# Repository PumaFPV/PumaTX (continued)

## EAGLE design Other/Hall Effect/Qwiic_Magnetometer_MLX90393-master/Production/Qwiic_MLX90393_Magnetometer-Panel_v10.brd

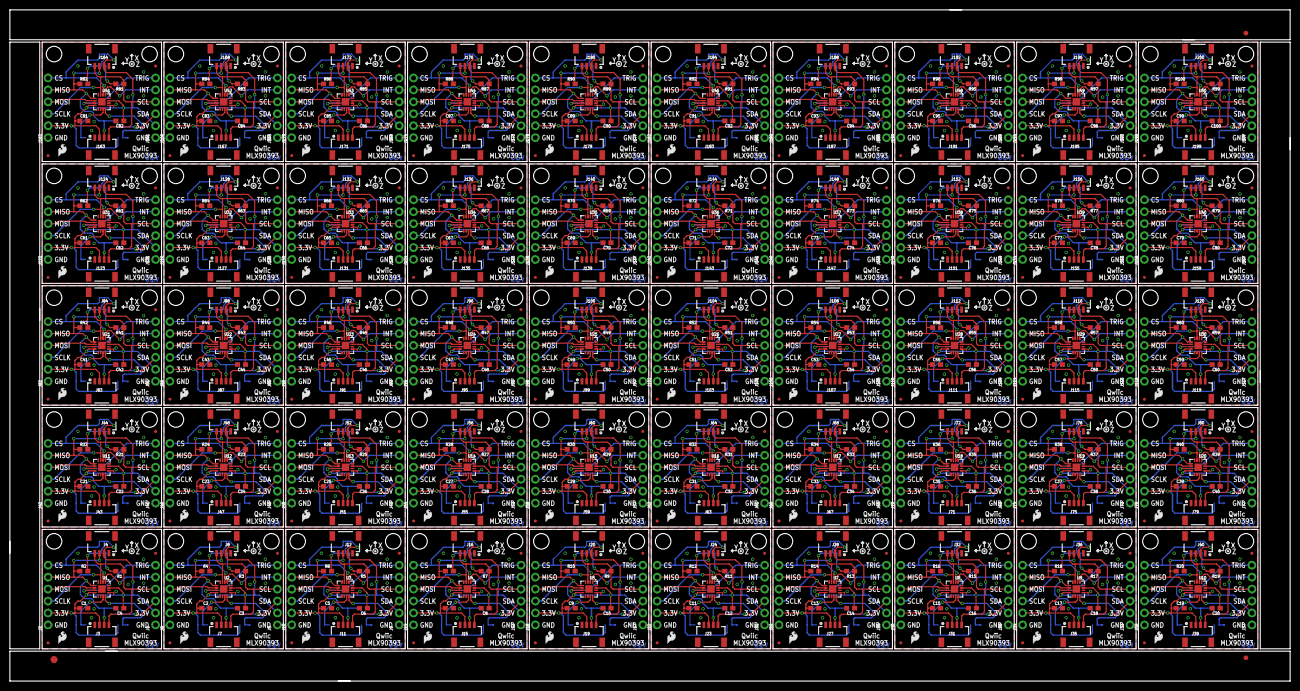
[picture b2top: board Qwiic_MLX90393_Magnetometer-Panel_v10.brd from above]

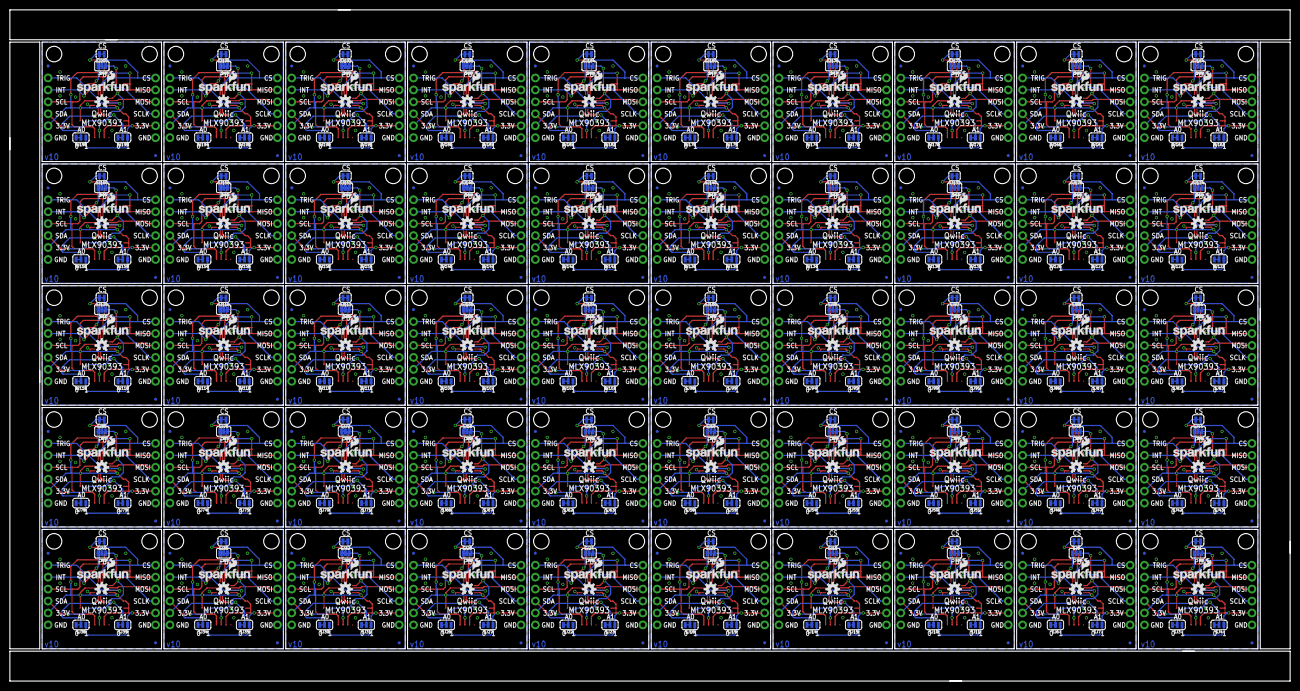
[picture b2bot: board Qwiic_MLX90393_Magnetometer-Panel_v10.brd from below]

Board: 2 copper layers, 272.3 x 142.7 mm, 1103 parts (400 on the bottom side), 600 nets.

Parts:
C1, C2, C3, C4, C5, C6, C7, C8, C9, C10, C11, C12, C13, C14, C15, C16, C17, C18, C19, C20, C21, C22, C23, C24, C25, C26, C27, C28, C29, C30, C31, C32, C33, C34, C35, C36, C37, C38, C39, C40, C41, C42, C43, C44, C45, C46, C47, C48, C49, C50, C51, C52, C53, C54, C55, C56, C57, C58, C59, C60, C61, C62, C63, C64, C65, C66, C67, C68, C69, C70, C71, C72, C73, C74, C75, C76, C77, C78, C79, C80, C81, C82, C83, C84, C85, C86, C87, C88, C89, C90, C91, C92, C93, C94, C95, C96, C97, C98, C99, C100: 0.1uF; 0603
E$1: FIDUCIAL-1.5X3
E$6, E$7: FIDUCIAL-1X2
FD1, FD2, FD3, FD4, FD5, FD6, FD7, FD8, FD9, FD10, FD11, FD12, FD13, FD14, FD15, FD16, FD17, FD18, FD19, FD20, FD21, FD22, FD23, FD24, FD25, FD26, FD27, FD28, FD29, FD30, FD31, FD32, FD33, FD34, FD35, FD36, FD37, FD38, FD39, FD40, FD41, FD42, FD43, FD44, FD45, FD46, FD47, FD48, FD49, FD50, FD51, FD52, FD53, FD54, FD55, FD56, FD57, FD58, FD59, FD60, FD61, FD62, FD63, FD64, FD65, FD66, FD67, FD68, FD69, FD70, FD71, FD72, FD73, FD74, FD75, FD76, FD77, FD78, FD79, FD80, FD81, FD82, FD83, FD84, FD85, FD86, FD87, FD88, FD89, FD90, FD91, FD92, FD93, FD94, FD95, FD96, FD97, FD98, FD99, FD100, FD101, FD102, FD103, FD104, FD105, FD106, FD107, FD108, FD109, FD110, FD111, FD112, FD113, FD114, FD115, FD116, FD117, FD118, FD119, FD120, FD121, FD122, FD123, FD124, FD125, FD126, FD127, FD128, FD129, FD130, FD131, FD132, FD133, FD134, FD135, FD136, FD137, FD138, FD139, FD140, FD141, FD142, FD143, FD144, FD145, FD146, FD147, FD148, FD149, FD150, FD151, FD152, FD153, FD154, FD155, FD156, FD157, FD158, FD159, FD160, FD161, FD162, FD163, FD164, FD165, FD166, FD167, FD168, FD169, FD170, FD171, FD172, FD173, FD174, FD175, FD176, FD177, FD178, FD179, FD180, FD181, FD182, FD183, FD184, FD185, FD186, FD187, FD188, FD189, FD190, FD191, FD192, FD193, FD194, FD195, FD196, FD197, FD198, FD199, FD200: FIDUCIALUFIDUCIAL; FIDUCIAL-MICRO
J1, J2, J5, J6, J9, J10, J13, J14, J17, J18, J21, J22, J25, J26, J29, J30, J33, J34, J37, J38, J41, J42, J45, J46, J49, J50, J53, J54, J57, J58, J61, J62, J65, J66, J69, J70, J73, J74, J77, J78, J81, J82, J85, J86, J89, J90, J93, J94, J97, J98, J101, J102, J105, J106, J109, J110, J113, J114, J117, J118, J121, J122, J125, J126, J129, J130, J133, J134, J137, J138, J141, J142, J145, J146, J149, J150, J153, J154, J157, J158, J161, J162, J165, J166, J169, J170, J173, J174, J177, J178, J181, J182, J185, J186, J189, J190, J193, J194, J197, J198: 1X06_NO_SILK
J3, J4, J7, J8, J11, J12, J15, J16, J19, J20, J23, J24, J27, J28, J31, J32, J35, J36, J39, J40, J43, J44, J47, J48, J51, J52, J55, J56, J59, J60, J63, J64, J67, J68, J71, J72, J75, J76, J79, J80, J83, J84, J87, J88, J91, J92, J95, J96, J99, J100, J103, J104, J107, J108, J111, J112, J115, J116, J119, J120, J123, J124, J127, J128, J131, J132, J135, J136, J139, J140, J143, J144, J147, J148, J151, J152, J155, J156, J159, J160, J163, J164, J167, J168, J171, J172, J175, J176, J179, J180, J183, J184, J187, J188, J191, J192, J195, J196, J199, J200: 1X04_1MM_RA
JP1, JP2, JP3, JP4, JP5, JP6, JP7, JP8, JP9, JP10, JP11, JP12, JP13, JP14, JP15, JP16, JP17, JP18, JP19, JP20, JP21, JP22, JP23, JP24, JP25, JP26, JP27, JP28, JP29, JP30, JP31, JP32, JP33, JP34, JP35, JP36, JP37, JP38, JP39, JP40, JP41, JP42, JP43, JP44, JP45, JP46, JP47, JP48, JP49, JP50, JP51, JP52, JP53, JP54, JP55, JP56, JP57, JP58, JP59, JP60, JP61, JP62, JP63, JP64, JP65, JP66, JP67, JP68, JP69, JP70, JP71, JP72, JP73, JP74, JP75, JP76, JP77, JP78, JP79, JP80, JP81, JP82, JP83, JP84, JP85, JP86, JP87, JP88, JP89, JP90, JP91, JP92, JP93, JP94, JP95, JP96, JP97, JP98, JP99, JP100: STAND-OFF
LOGO1, LOGO3, LOGO5, LOGO7, LOGO9, LOGO11, LOGO13, LOGO15, LOGO17, LOGO19, LOGO21, LOGO23, LOGO25, LOGO27, LOGO29, LOGO31, LOGO33, LOGO35, LOGO37, LOGO39, LOGO41, LOGO43, LOGO45, LOGO47, LOGO49, LOGO51, LOGO53, LOGO55, LOGO57, LOGO59, LOGO61, LOGO63, LOGO65, LOGO67, LOGO69, LOGO71, LOGO73, LOGO75, LOGO77, LOGO79, LOGO81, LOGO83, LOGO85, LOGO87, LOGO89, LOGO91, LOGO93, LOGO95, LOGO97, LOGO99: SFE_LOGO_NAME_FLAME.1_INCH; SFE_LOGO_NAME_FLAME_.1
LOGO2, LOGO4, LOGO6, LOGO8, LOGO10, LOGO12, LOGO14, LOGO16, LOGO18, LOGO20, LOGO22, LOGO24, LOGO26, LOGO28, LOGO30, LOGO32, LOGO34, LOGO36, LOGO38, LOGO40, LOGO42, LOGO44, LOGO46, LOGO48, LOGO50, LOGO52, LOGO54, LOGO56, LOGO58, LOGO60, LOGO62, LOGO64, LOGO66, LOGO68, LOGO70, LOGO72, LOGO74, LOGO76, LOGO78, LOGO80, LOGO82, LOGO84, LOGO86, LOGO88, LOGO90, LOGO92, LOGO94, LOGO96, LOGO98, LOGO100: SFE_LOGO_FLAME.1_INCH; SFE_LOGO_FLAME_.1
R1, R2, R3, R4, R5, R6, R7, R8, R9, R10, R11, R12, R13, R14, R15, R16, R17, R18, R19, R20, R21, R22, R23, R24, R25, R26, R27, R28, R29, R30, R31, R32, R33, R34, R35, R36, R37, R38, R39, R40, R41, R42, R43, R44, R45, R46, R47, R48, R49, R50, R51, R52, R53, R54, R55, R56, R57, R58, R59, R60, R61, R62, R63, R64, R65, R66, R67, R68, R69, R70, R71, R72, R73, R74, R75, R76, R77, R78, R79, R80, R81, R82, R83, R84, R85, R86, R87, R88, R89, R90, R91, R92, R93, R94, R95, R96, R97, R98, R99, R100: 10k; 0603
SJ1, SJ8, SJ12, SJ16, SJ20, SJ24, SJ28, SJ32, SJ36, SJ40, SJ44, SJ48, SJ52, SJ56, SJ60, SJ64, SJ68, SJ72, SJ76, SJ80, SJ84, SJ88, SJ92, SJ96, SJ100, SJ104, SJ108, SJ112, SJ116, SJ120, SJ124, SJ128, SJ132, SJ136, SJ140, SJ144, SJ148, SJ152, SJ156, SJ160, SJ164, SJ168, SJ172, SJ176, SJ180, SJ184, SJ188, SJ192, SJ196, SJ200: SMT-JUMPER_2_NC_TRACE_SILK
SJ2, SJ5, SJ9, SJ13, SJ17, SJ21, SJ25, SJ29, SJ33, SJ37, SJ41, SJ45, SJ49, SJ53, SJ57, SJ61, SJ65, SJ69, SJ73, SJ77, SJ81, SJ85, SJ89, SJ93, SJ97, SJ101, SJ105, SJ109, SJ113, SJ117, SJ121, SJ125, SJ129, SJ133, SJ137, SJ141, SJ145, SJ149, SJ153, SJ157, SJ161, SJ165, SJ169, SJ173, SJ177, SJ181, SJ185, SJ189, SJ193, SJ197: PAD-JUMPER-3-3OF3_NC_BY_TRACE_YES_SILK_FULL_BOX
SJ3, SJ4, SJ6, SJ7, SJ10, SJ11, SJ14, SJ15, SJ18, SJ19, SJ22, SJ23, SJ26, SJ27, SJ30, SJ31, SJ34, SJ35, SJ38, SJ39, SJ42, SJ43, SJ46, SJ47, SJ50, SJ51, SJ54, SJ55, SJ58, SJ59, SJ62, SJ63, SJ66, SJ67, SJ70, SJ71, SJ74, SJ75, SJ78, SJ79, SJ82, SJ83, SJ86, SJ87, SJ90, SJ91, SJ94, SJ95, SJ98, SJ99, SJ102, SJ103, SJ106, SJ107, SJ110, SJ111, SJ114, SJ115, SJ118, SJ119, SJ122, SJ123, SJ126, SJ127, SJ130, SJ131, SJ134, SJ135, SJ138, SJ139, SJ142, SJ143, SJ146, SJ147, SJ150, SJ151, SJ154, SJ155, SJ158, SJ159, SJ162, SJ163, SJ166, SJ167, SJ170, SJ171, SJ174, SJ175, SJ178, SJ179, SJ182, SJ183, SJ186, SJ187, SJ190, SJ191, SJ194, SJ195, SJ198, SJ199: SMT-JUMPER_3_1-NC_TRACE_SILK
U1, U2, U3, U4, U5, U6, U7, U8, U9, U10, U11, U12, U13, U14, U15, U16, U17, U18, U19, U20, U21, U22, U23, U24, U25, U26, U27, U28, U29, U30, U31, U32, U33, U34, U35, U36, U37, U38, U39, U40, U41, U42, U43, U44, U45, U46, U47, U48, U49, U50: MLX90393_MAGNETOMETER; QFN-16_WITH_AXIES
U$1, U$2, U$3, U$4, U$5, U$6, U$7, U$8, U$9, U$10, U$11, U$12, U$13, U$14, U$15, U$16, U$17, U$18, U$19, U$20, U$21, U$22, U$23, U$24, U$25, U$26, U$27, U$28, U$29, U$30, U$31, U$32, U$33, U$34, U$35, U$36, U$37, U$38, U$39, U$40, U$41, U$42, U$43, U$44, U$45, U$46, U$47, U$48, U$49, U$50: OSHW-LOGOS; OSHW-LOGO-S

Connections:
3.3V: C1.1, C4.1, J1.2, J2.2, J3.2, J4.2, SJ1.2, SJ2.2, SJ3.1, SJ4.1, U1.8, U1.15
3.3V1: C2.1, C3.1, J5.2, J6.2, J7.2, J8.2, SJ5.2, SJ6.1, SJ7.1, SJ8.2, U2.8, U2.15
3.3V2: C5.1, C6.1, J9.2, J10.2, J11.2, J12.2, SJ9.2, SJ10.1, SJ11.1, SJ12.2, U3.8, U3.15
3.3V3: C7.1, C8.1, J13.2, J14.2, J15.2, J16.2, SJ13.2, SJ14.1, SJ15.1, SJ16.2, U4.8, U4.15
3.3V4: C9.1, C10.1, J17.2, J18.2, J19.2, J20.2, SJ17.2, SJ18.1, SJ19.1, SJ20.2, U5.8, U5.15
3.3V5: C11.1, C12.1, J21.2, J22.2, J23.2, J24.2, SJ21.2, SJ22.1, SJ23.1, SJ24.2, U6.8, U6.15
3.3V6: C13.1, C14.1, J25.2, J26.2, J27.2, J28.2, SJ25.2, SJ26.1, SJ27.1, SJ28.2, U7.8, U7.15
3.3V7: C15.1, C16.1, J29.2, J30.2, J31.2, J32.2, SJ29.2, SJ30.1, SJ31.1, SJ32.2, U8.8, U8.15
3.3V8: C17.1, C18.1, J33.2, J34.2, J35.2, J36.2, SJ33.2, SJ34.1, SJ35.1, SJ36.2, U9.8, U9.15
3.3V9: C19.1, C20.1, J37.2, J38.2, J39.2, J40.2, SJ37.2, SJ38.1, SJ39.1, SJ40.2, U10.8, U10.15
3.3V10: C21.1, C22.1, J41.2, J42.2, J43.2, J44.2, SJ41.2, SJ42.1, SJ43.1, SJ44.2, U11.8, U11.15
3.3V11: C23.1, C24.1, J45.2, J46.2, J47.2, J48.2, SJ45.2, SJ46.1, SJ47.1, SJ48.2, U12.8, U12.15
3.3V12: C25.1, C26.1, J49.2, J50.2, J51.2, J52.2, SJ49.2, SJ50.1, SJ51.1, SJ52.2, U13.8, U13.15
3.3V13: C27.1, C28.1, J53.2, J54.2, J55.2, J56.2, SJ53.2, SJ54.1, SJ55.1, SJ56.2, U14.8, U14.15
3.3V14: C29.1, C30.1, J57.2, J58.2, J59.2, J60.2, SJ57.2, SJ58.1, SJ59.1, SJ60.2, U15.8, U15.15
3.3V15: C31.1, C32.1, J61.2, J62.2, J63.2, J64.2, SJ61.2, SJ62.1, SJ63.1, SJ64.2, U16.8, U16.15
3.3V16: C33.1, C34.1, J65.2, J66.2, J67.2, J68.2, SJ65.2, SJ66.1, SJ67.1, SJ68.2, U17.8, U17.15
3.3V17: C35.1, C36.1, J69.2, J70.2, J71.2, J72.2, SJ69.2, SJ70.1, SJ71.1, SJ72.2, U18.8, U18.15
3.3V18: C37.1, C38.1, J73.2, J74.2, J75.2, J76.2, SJ73.2, SJ74.1, SJ75.1, SJ76.2, U19.8, U19.15
3.3V19: C39.1, C40.1, J77.2, J78.2, J79.2, J80.2, SJ77.2, SJ78.1, SJ79.1, SJ80.2, U20.8, U20.15
3.3V20: C41.1, C42.1, J81.2, J82.2, J83.2, J84.2, SJ81.2, SJ82.1, SJ83.1, SJ84.2, U21.8, U21.15
3.3V21: C43.1, C44.1, J85.2, J86.2, J87.2, J88.2, SJ85.2, SJ86.1, SJ87.1, SJ88.2, U22.8, U22.15
3.3V22: C45.1, C46.1, J89.2, J90.2, J91.2, J92.2, SJ89.2, SJ90.1, SJ91.1, SJ92.2, U23.8, U23.15
3.3V23: C47.1, C48.1, J93.2, J94.2, J95.2, J96.2, SJ93.2, SJ94.1, SJ95.1, SJ96.2, U24.8, U24.15
3.3V24: C49.1, C50.1, J97.2, J98.2, J99.2, J100.2, SJ97.2, SJ98.1, SJ99.1, SJ100.2, U25.8, U25.15
3.3V25: C51.1, C52.1, J101.2, J102.2, J103.2, J104.2, SJ101.2, SJ102.1, SJ103.1, SJ104.2, U26.8, U26.15
3.3V26: C53.1, C54.1, J105.2, J106.2, J107.2, J108.2, SJ105.2, SJ106.1, SJ107.1, SJ108.2, U27.8, U27.15
3.3V27: C55.1, C56.1, J109.2, J110.2, J111.2, J112.2, SJ109.2, SJ110.1, SJ111.1, SJ112.2, U28.8, U28.15
3.3V28: C57.1, C58.1, J113.2, J114.2, J115.2, J116.2, SJ113.2, SJ114.1, SJ115.1, SJ116.2, U29.8, U29.15
3.3V29: C59.1, C60.1, J117.2, J118.2, J119.2, J120.2, SJ117.2, SJ118.1, SJ119.1, SJ120.2, U30.8, U30.15
3.3V30: C61.1, C62.1, J121.2, J122.2, J123.2, J124.2, SJ121.2, SJ122.1, SJ123.1, SJ124.2, U31.8, U31.15
3.3V31: C63.1, C64.1, J125.2, J126.2, J127.2, J128.2, SJ125.2, SJ126.1, SJ127.1, SJ128.2, U32.8, U32.15
3.3V32: C65.1, C66.1, J129.2, J130.2, J131.2, J132.2, SJ129.2, SJ130.1, SJ131.1, SJ132.2, U33.8, U33.15
3.3V33: C67.1, C68.1, J133.2, J134.2, J135.2, J136.2, SJ133.2, SJ134.1, SJ135.1, SJ136.2, U34.8, U34.15
3.3V34: C69.1, C70.1, J137.2, J138.2, J139.2, J140.2, SJ137.2, SJ138.1, SJ139.1, SJ140.2, U35.8, U35.15
3.3V35: C71.1, C72.1, J141.2, J142.2, J143.2, J144.2, SJ141.2, SJ142.1, SJ143.1, SJ144.2, U36.8, U36.15
3.3V36: C73.1, C74.1, J145.2, J146.2, J147.2, J148.2, SJ145.2, SJ146.1, SJ147.1, SJ148.2, U37.8, U37.15
3.3V37: C75.1, C76.1, J149.2, J150.2, J151.2, J152.2, SJ149.2, SJ150.1, SJ151.1, SJ152.2, U38.8, U38.15
3.3V38: C77.1, C78.1, J153.2, J154.2, J155.2, J156.2, SJ153.2, SJ154.1, SJ155.1, SJ156.2, U39.8, U39.15
3.3V39: C79.1, C80.1, J157.2, J158.2, J159.2, J160.2, SJ157.2, SJ158.1, SJ159.1, SJ160.2, U40.8, U40.15
3.3V40: C81.1, C82.1, J161.2, J162.2, J163.2, J164.2, SJ161.2, SJ162.1, SJ163.1, SJ164.2, U41.8, U41.15
3.3V41: C83.1, C84.1, J165.2, J166.2, J167.2, J168.2, SJ165.2, SJ166.1, SJ167.1, SJ168.2, U42.8, U42.15
3.3V42: C85.1, C86.1, J169.2, J170.2, J171.2, J172.2, SJ169.2, SJ170.1, SJ171.1, SJ172.2, U43.8, U43.15
3.3V43: C87.1, C88.1, J173.2, J174.2, J175.2, J176.2, SJ173.2, SJ174.1, SJ175.1, SJ176.2, U44.8, U44.15
3.3V44: C89.1, C90.1, J177.2, J178.2, J179.2, J180.2, SJ177.2, SJ178.1, SJ179.1, SJ180.2, U45.8, U45.15
3.3V45: C91.1, C92.1, J181.2, J182.2, J183.2, J184.2, SJ181.2, SJ182.1, SJ183.1, SJ184.2, U46.8, U46.15
3.3V46: C93.1, C94.1, J185.2, J186.2, J187.2, J188.2, SJ185.2, SJ186.1, SJ187.1, SJ188.2, U47.8, U47.15
3.3V47: C95.1, C96.1, J189.2, J190.2, J191.2, J192.2, SJ189.2, SJ190.1, SJ191.1, SJ192.2, U48.8, U48.15
3.3V48: C97.1, C98.1, J193.2, J194.2, J195.2, J196.2, SJ193.2, SJ194.1, SJ195.1, SJ196.2, U49.8, U49.15
3.3V49: C99.1, C100.1, J197.2, J198.2, J199.2, J200.2, SJ197.2, SJ198.1, SJ199.1, SJ200.2, U50.8, U50.15
A0: SJ3.2, U1.12
A1: SJ4.2, U1.11
A2: SJ6.2, U2.12
A3: SJ7.2, U2.11
A4: SJ10.2, U3.12
A5: SJ11.2, U3.11
A6: SJ14.2, U4.12
A7: SJ15.2, U4.11
A8: SJ18.2, U5.12
A9: SJ19.2, U5.11
A10: SJ22.2, U6.12
A11: SJ23.2, U6.11
A12: SJ26.2, U7.12
A13: SJ27.2, U7.11
A14: SJ30.2, U8.12
A15: SJ31.2, U8.11
A16: SJ34.2, U9.12
A17: SJ35.2, U9.11
A18: SJ38.2, U10.12
A19: SJ39.2, U10.11
A20: SJ42.2, U11.12
A21: SJ43.2, U11.11
A22: SJ46.2, U12.12
A23: SJ47.2, U12.11
A24: SJ50.2, U13.12
A25: SJ51.2, U13.11
A26: SJ54.2, U14.12
A27: SJ55.2, U14.11
A28: SJ58.2, U15.12
A29: SJ59.2, U15.11
A30: SJ62.2, U16.12
A31: SJ63.2, U16.11
A32: SJ66.2, U17.12
A33: SJ67.2, U17.11
A34: SJ70.2, U18.12
A35: SJ71.2, U18.11
A36: SJ74.2, U19.12
A37: SJ75.2, U19.11
A38: SJ78.2, U20.12
A39: SJ79.2, U20.11
A40: SJ82.2, U21.12
A41: SJ83.2, U21.11
A42: SJ86.2, U22.12
A43: SJ87.2, U22.11
A44: SJ90.2, U23.12
A45: SJ91.2, U23.11
A46: SJ94.2, U24.12
A47: SJ95.2, U24.11
A48: SJ98.2, U25.12
A49: SJ99.2, U25.11
A50: SJ102.2, U26.12
A51: SJ103.2, U26.11
A52: SJ106.2, U27.12
A53: SJ107.2, U27.11
A54: SJ110.2, U28.12
A55: SJ111.2, U28.11
A56: SJ114.2, U29.12
A57: SJ115.2, U29.11
A58: SJ118.2, U30.12
A59: SJ119.2, U30.11
A60: SJ122.2, U31.12
A61: SJ123.2, U31.11
A62: SJ126.2, U32.12
A63: SJ127.2, U32.11
A64: SJ130.2, U33.12
A65: SJ131.2, U33.11
A66: SJ134.2, U34.12
A67: SJ135.2, U34.11
A68: SJ138.2, U35.12
A69: SJ139.2, U35.11
A70: SJ142.2, U36.12
A71: SJ143.2, U36.11
A72: SJ146.2, U37.12
A73: SJ147.2, U37.11
A74: SJ150.2, U38.12
A75: SJ151.2, U38.11
A76: SJ154.2, U39.12
A77: SJ155.2, U39.11
A78: SJ158.2, U40.12
A79: SJ159.2, U40.11
A80: SJ162.2, U41.12
A81: SJ163.2, U41.11
A82: SJ166.2, U42.12
A83: SJ167.2, U42.11
A84: SJ170.2, U43.12
A85: SJ171.2, U43.11
A86: SJ174.2, U44.12
A87: SJ175.2, U44.11
A88: SJ178.2, U45.12
A89: SJ179.2, U45.11
A90: SJ182.2, U46.12
A91: SJ183.2, U46.11
A92: SJ186.2, U47.12
A93: SJ187.2, U47.11
A94: SJ190.2, U48.12
A95: SJ191.2, U48.11
A96: SJ194.2, U49.12
A97: SJ195.2, U49.11
A98: SJ198.2, U50.12
A99: SJ199.2, U50.11
CS: J2.6, SJ1.1, U1.2
CS1: J6.6, SJ8.1, U2.2
CS2: J10.6, SJ12.1, U3.2
CS3: J14.6, SJ16.1, U4.2
CS4: J18.6, SJ20.1, U5.2
CS5: J22.6, SJ24.1, U6.2
CS6: J26.6, SJ28.1, U7.2
CS7: J30.6, SJ32.1, U8.2
CS8: J34.6, SJ36.1, U9.2
CS9: J38.6, SJ40.1, U10.2
CS10: J42.6, SJ44.1, U11.2
CS11: J46.6, SJ48.1, U12.2
CS12: J50.6, SJ52.1, U13.2
CS13: J54.6, SJ56.1, U14.2
CS14: J58.6, SJ60.1, U15.2
CS15: J62.6, SJ64.1, U16.2
CS16: J66.6, SJ68.1, U17.2
CS17: J70.6, SJ72.1, U18.2
CS18: J74.6, SJ76.1, U19.2
CS19: J78.6, SJ80.1, U20.2
CS20: J82.6, SJ84.1, U21.2
CS21: J86.6, SJ88.1, U22.2
CS22: J90.6, SJ92.1, U23.2
CS23: J94.6, SJ96.1, U24.2
CS24: J98.6, SJ100.1, U25.2
CS25: J102.6, SJ104.1, U26.2
CS26: J106.6, SJ108.1, U27.2
CS27: J110.6, SJ112.1, U28.2
CS28: J114.6, SJ116.1, U29.2
CS29: J118.6, SJ120.1, U30.2
CS30: J122.6, SJ124.1, U31.2
CS31: J126.6, SJ128.1, U32.2
CS32: J130.6, SJ132.1, U33.2
CS33: J134.6, SJ136.1, U34.2
CS34: J138.6, SJ140.1, U35.2
CS35: J142.6, SJ144.1, U36.2
CS36: J146.6, SJ148.1, U37.2
CS37: J150.6, SJ152.1, U38.2
CS38: J154.6, SJ156.1, U39.2
CS39: J158.6, SJ160.1, U40.2
CS40: J162.6, SJ164.1, U41.2
CS41: J166.6, SJ168.1, U42.2
CS42: J170.6, SJ172.1, U43.2
CS43: J174.6, SJ176.1, U44.2
CS44: J178.6, SJ180.1, U45.2
CS45: J182.6, SJ184.1, U46.2
CS46: J186.6, SJ188.1, U47.2
CS47: J190.6, SJ192.1, U48.2
CS48: J194.6, SJ196.1, U49.2
CS49: J198.6, SJ200.1, U50.2
GND: C1.2, C4.2, J1.1, J2.1, J3.1, J4.1, SJ3.3, SJ4.3, U1.13
GND1: C2.2, C3.2, J5.1, J6.1, J7.1, J8.1, SJ6.3, SJ7.3, U2.13
GND2: C5.2, C6.2, J9.1, J10.1, J11.1, J12.1, SJ10.3, SJ11.3, U3.13
GND3: C7.2, C8.2, J13.1, J14.1, J15.1, J16.1, SJ14.3, SJ15.3, U4.13
GND4: C9.2, C10.2, J17.1, J18.1, J19.1, J20.1, SJ18.3, SJ19.3, U5.13
GND5: C11.2, C12.2, J21.1, J22.1, J23.1, J24.1, SJ22.3, SJ23.3, U6.13
GND6: C13.2, C14.2, J25.1, J26.1, J27.1, J28.1, SJ26.3, SJ27.3, U7.13
GND7: C15.2, C16.2, J29.1, J30.1, J31.1, J32.1, SJ30.3, SJ31.3, U8.13
GND8: C17.2, C18.2, J33.1, J34.1, J35.1, J36.1, SJ34.3, SJ35.3, U9.13
GND9: C19.2, C20.2, J37.1, J38.1, J39.1, J40.1, SJ38.3, SJ39.3, U10.13
GND10: C21.2, C22.2, J41.1, J42.1, J43.1, J44.1, SJ42.3, SJ43.3, U11.13
GND11: C23.2, C24.2, J45.1, J46.1, J47.1, J48.1, SJ46.3, SJ47.3, U12.13
GND12: C25.2, C26.2, J49.1, J50.1, J51.1, J52.1, SJ50.3, SJ51.3, U13.13
GND13: C27.2, C28.2, J53.1, J54.1, J55.1, J56.1, SJ54.3, SJ55.3, U14.13
GND14: C29.2, C30.2, J57.1, J58.1, J59.1, J60.1, SJ58.3, SJ59.3, U15.13
GND15: C31.2, C32.2, J61.1, J62.1, J63.1, J64.1, SJ62.3, SJ63.3, U16.13
GND16: C33.2, C34.2, J65.1, J66.1, J67.1, J68.1, SJ66.3, SJ67.3, U17.13
GND17: C35.2, C36.2, J69.1, J70.1, J71.1, J72.1, SJ70.3, SJ71.3, U18.13
GND18: C37.2, C38.2, J73.1, J74.1, J75.1, J76.1, SJ74.3, SJ75.3, U19.13
GND19: C39.2, C40.2, J77.1, J78.1, J79.1, J80.1, SJ78.3, SJ79.3, U20.13
GND20: C41.2, C42.2, J81.1, J82.1, J83.1, J84.1, SJ82.3, SJ83.3, U21.13
GND21: C43.2, C44.2, J85.1, J86.1, J87.1, J88.1, SJ86.3, SJ87.3, U22.13
GND22: C45.2, C46.2, J89.1, J90.1, J91.1, J92.1, SJ90.3, SJ91.3, U23.13
GND23: C47.2, C48.2, J93.1, J94.1, J95.1, J96.1, SJ94.3, SJ95.3, U24.13
GND24: C49.2, C50.2, J97.1, J98.1, J99.1, J100.1, SJ98.3, SJ99.3, U25.13
GND25: C51.2, C52.2, J101.1, J102.1, J103.1, J104.1, SJ102.3, SJ103.3, U26.13
GND26: C53.2, C54.2, J105.1, J106.1, J107.1, J108.1, SJ106.3, SJ107.3, U27.13
GND27: C55.2, C56.2, J109.1, J110.1, J111.1, J112.1, SJ110.3, SJ111.3, U28.13
GND28: C57.2, C58.2, J113.1, J114.1, J115.1, J116.1, SJ114.3, SJ115.3, U29.13
GND29: C59.2, C60.2, J117.1, J118.1, J119.1, J120.1, SJ118.3, SJ119.3, U30.13
GND30: C61.2, C62.2, J121.1, J122.1, J123.1, J124.1, SJ122.3, SJ123.3, U31.13
GND31: C63.2, C64.2, J125.1, J126.1, J127.1, J128.1, SJ126.3, SJ127.3, U32.13
GND32: C65.2, C66.2, J129.1, J130.1, J131.1, J132.1, SJ130.3, SJ131.3, U33.13
GND33: C67.2, C68.2, J133.1, J134.1, J135.1, J136.1, SJ134.3, SJ135.3, U34.13
GND34: C69.2, C70.2, J137.1, J138.1, J139.1, J140.1, SJ138.3, SJ139.3, U35.13
GND35: C71.2, C72.2, J141.1, J142.1, J143.1, J144.1, SJ142.3, SJ143.3, U36.13
GND36: C73.2, C74.2, J145.1, J146.1, J147.1, J148.1, SJ146.3, SJ147.3, U37.13
GND37: C75.2, C76.2, J149.1, J150.1, J151.1, J152.1, SJ150.3, SJ151.3, U38.13
GND38: C77.2, C78.2, J153.1, J154.1, J155.1, J156.1, SJ154.3, SJ155.3, U39.13
GND39: C79.2, C80.2, J157.1, J158.1, J159.1, J160.1, SJ158.3, SJ159.3, U40.13
GND40: C81.2, C82.2, J161.1, J162.1, J163.1, J164.1, SJ162.3, SJ163.3, U41.13
GND41: C83.2, C84.2, J165.1, J166.1, J167.1, J168.1, SJ166.3, SJ167.3, U42.13
GND42: C85.2, C86.2, J169.1, J170.1, J171.1, J172.1, SJ170.3, SJ171.3, U43.13
GND43: C87.2, C88.2, J173.1, J174.1, J175.1, J176.1, SJ174.3, SJ175.3, U44.13
GND44: C89.2, C90.2, J177.1, J178.1, J179.1, J180.1, SJ178.3, SJ179.3, U45.13
GND45: C91.2, C92.2, J181.1, J182.1, J183.1, J184.1, SJ182.3, SJ183.3, U46.13
GND46: C93.2, C94.2, J185.1, J186.1, J187.1, J188.1, SJ186.3, SJ187.3, U47.13
GND47: C95.2, C96.2, J189.1, J190.1, J191.1, J192.1, SJ190.3, SJ191.3, U48.13
GND48: C97.2, C98.2, J193.1, J194.1, J195.1, J196.1, SJ194.3, SJ195.3, U49.13
GND49: C99.2, C100.2, J197.1, J198.1, J199.1, J200.1, SJ198.3, SJ199.3, U50.13
INT: J1.5, U1.1
INT1: J5.5, U2.1
INT2: J9.5, U3.1
INT3: J13.5, U4.1
INT4: J17.5, U5.1
INT5: J21.5, U6.1
INT6: J25.5, U7.1
INT7: J29.5, U8.1
INT8: J33.5, U9.1
INT9: J37.5, U10.1
INT10: J41.5, U11.1
INT11: J45.5, U12.1
INT12: J49.5, U13.1
INT13: J53.5, U14.1
INT14: J57.5, U15.1
INT15: J61.5, U16.1
INT16: J65.5, U17.1
INT17: J69.5, U18.1
INT18: J73.5, U19.1
INT19: J77.5, U20.1
INT20: J81.5, U21.1
INT21: J85.5, U22.1
INT22: J89.5, U23.1
INT23: J93.5, U24.1
INT24: J97.5, U25.1
INT25: J101.5, U26.1
INT26: J105.5, U27.1
INT27: J109.5, U28.1
INT28: J113.5, U29.1
INT29: J117.5, U30.1
INT30: J121.5, U31.1
INT31: J125.5, U32.1
INT32: J129.5, U33.1
INT33: J133.5, U34.1
INT34: J137.5, U35.1
INT35: J141.5, U36.1
INT36: J145.5, U37.1
INT37: J149.5, U38.1
INT38: J153.5, U39.1
INT39: J157.5, U40.1
INT40: J161.5, U41.1
INT41: J165.5, U42.1
INT42: J169.5, U43.1
INT43: J173.5, U44.1
INT44: J177.5, U45.1
INT45: J181.5, U46.1
INT46: J185.5, U47.1
INT47: J189.5, U48.1
INT48: J193.5, U49.1
INT49: J197.5, U50.1
MISO: J2.4, U1.6
MISO1: J6.4, U2.6
MISO2: J10.4, U3.6
MISO3: J14.4, U4.6
MISO4: J18.4, U5.6
MISO5: J22.4, U6.6
MISO6: J26.4, U7.6
MISO7: J30.4, U8.6
MISO8: J34.4, U9.6
MISO9: J38.4, U10.6
MISO10: J42.4, U11.6
MISO11: J46.4, U12.6
MISO12: J50.4, U13.6
MISO13: J54.4, U14.6
MISO14: J58.4, U15.6
MISO15: J62.4, U16.6
MISO16: J66.4, U17.6
MISO17: J70.4, U18.6
MISO18: J74.4, U19.6
MISO19: J78.4, U20.6
MISO20: J82.4, U21.6
MISO21: J86.4, U22.6
MISO22: J90.4, U23.6
MISO23: J94.4, U24.6
MISO24: J98.4, U25.6
MISO25: J102.4, U26.6
MISO26: J106.4, U27.6
MISO27: J110.4, U28.6
MISO28: J114.4, U29.6
MISO29: J118.4, U30.6
MISO30: J122.4, U31.6
MISO31: J126.4, U32.6
MISO32: J130.4, U33.6
MISO33: J134.4, U34.6
MISO34: J138.4, U35.6
MISO35: J142.4, U36.6
MISO36: J146.4, U37.6
MISO37: J150.4, U38.6
MISO38: J154.4, U39.6
MISO39: J158.4, U40.6
MISO40: J162.4, U41.6
MISO41: J166.4, U42.6
MISO42: J170.4, U43.6
MISO43: J174.4, U44.6
MISO44: J178.4, U45.6
MISO45: J182.4, U46.6
MISO46: J186.4, U47.6
MISO47: J190.4, U48.6
MISO48: J194.4, U49.6
MISO49: J198.4, U50.6
unnamed: R4.2, SJ5.1
unnamed: R3.2, SJ5.3
unnamed: R6.2, SJ9.1
unnamed: R2.2, SJ2.1
unnamed: R1.2, SJ2.3
unnamed: R5.2, SJ9.3
unnamed: R8.2, SJ13.1
unnamed: R7.2, SJ13.3
unnamed: R10.2, SJ17.1
unnamed: R9.2, SJ17.3
unnamed: R12.2, SJ21.1
unnamed: R11.2, SJ21.3
unnamed: R14.2, SJ25.1
unnamed: R13.2, SJ25.3
unnamed: R16.2, SJ29.1
unnamed: R15.2, SJ29.3
unnamed: R18.2, SJ33.1
unnamed: R17.2, SJ33.3
unnamed: R20.2, SJ37.1
unnamed: R19.2, SJ37.3
unnamed: R22.2, SJ41.1
unnamed: R21.2, SJ41.3
unnamed: R24.2, SJ45.1
unnamed: R23.2, SJ45.3
unnamed: R26.2, SJ49.1
unnamed: R25.2, SJ49.3
unnamed: R28.2, SJ53.1
unnamed: R27.2, SJ53.3
unnamed: R30.2, SJ57.1
unnamed: R29.2, SJ57.3
unnamed: R32.2, SJ61.1
unnamed: R31.2, SJ61.3
unnamed: R34.2, SJ65.1
unnamed: R33.2, SJ65.3
unnamed: R36.2, SJ69.1
unnamed: R35.2, SJ69.3
unnamed: R38.2, SJ73.1
unnamed: R37.2, SJ73.3
unnamed: R40.2, SJ77.1
unnamed: R39.2, SJ77.3
unnamed: R42.2, SJ81.1
unnamed: R41.2, SJ81.3
unnamed: R44.2, SJ85.1
unnamed: R43.2, SJ85.3
unnamed: R46.2, SJ89.1
unnamed: R45.2, SJ89.3
unnamed: R48.2, SJ93.1
unnamed: R47.2, SJ93.3
unnamed: R50.2, SJ97.1
unnamed: R49.2, SJ97.3
unnamed: R52.2, SJ101.1
unnamed: R51.2, SJ101.3
unnamed: R54.2, SJ105.1
unnamed: R53.2, SJ105.3
unnamed: R56.2, SJ109.1
unnamed: R55.2, SJ109.3
unnamed: R58.2, SJ113.1
unnamed: R57.2, SJ113.3
unnamed: R60.2, SJ117.1
unnamed: R59.2, SJ117.3
unnamed: R62.2, SJ121.1
unnamed: R61.2, SJ121.3
unnamed: R64.2, SJ125.1
unnamed: R63.2, SJ125.3
unnamed: R66.2, SJ129.1
unnamed: R65.2, SJ129.3
unnamed: R68.2, SJ133.1
unnamed: R67.2, SJ133.3
unnamed: R70.2, SJ137.1
unnamed: R69.2, SJ137.3
unnamed: R72.2, SJ141.1
unnamed: R71.2, SJ141.3
unnamed: R74.2, SJ145.1
unnamed: R73.2, SJ145.3
unnamed: R76.2, SJ149.1
unnamed: R75.2, SJ149.3
unnamed: R78.2, SJ153.1
unnamed: R77.2, SJ153.3
unnamed: R80.2, SJ157.1
unnamed: R79.2, SJ157.3
unnamed: R82.2, SJ161.1
unnamed: R81.2, SJ161.3
unnamed: R84.2, SJ165.1
unnamed: R83.2, SJ165.3
unnamed: R86.2, SJ169.1
unnamed: R85.2, SJ169.3
unnamed: R88.2, SJ173.1
unnamed: R87.2, SJ173.3
unnamed: R90.2, SJ177.1
unnamed: R89.2, SJ177.3
unnamed: R92.2, SJ181.1
unnamed: R91.2, SJ181.3
unnamed: R94.2, SJ185.1
unnamed: R93.2, SJ185.3
unnamed: R96.2, SJ189.1
unnamed: R95.2, SJ189.3
unnamed: R98.2, SJ193.1
unnamed: R97.2, SJ193.3
unnamed: R100.2, SJ197.1
unnamed: R99.2, SJ197.3
SCL: J1.4, J2.3, J3.4, J4.4, R1.1, U1.3
SCL1: J5.4, J6.3, J7.4, J8.4, R3.1, U2.3
SCL2: J9.4, J10.3, J11.4, J12.4, R5.1, U3.3
SCL3: J13.4, J14.3, J15.4, J16.4, R7.1, U4.3
SCL4: J17.4, J18.3, J19.4, J20.4, R9.1, U5.3
SCL5: J21.4, J22.3, J23.4, J24.4, R11.1, U6.3
SCL6: J25.4, J26.3, J27.4, J28.4, R13.1, U7.3
SCL7: J29.4, J30.3, J31.4, J32.4, R15.1, U8.3
SCL8: J33.4, J34.3, J35.4, J36.4, R17.1, U9.3
SCL9: J37.4, J38.3, J39.4, J40.4, R19.1, U10.3
SCL10: J41.4, J42.3, J43.4, J44.4, R21.1, U11.3
SCL11: J45.4, J46.3, J47.4, J48.4, R23.1, U12.3
SCL12: J49.4, J50.3, J51.4, J52.4, R25.1, U13.3
SCL13: J53.4, J54.3, J55.4, J56.4, R27.1, U14.3
SCL14: J57.4, J58.3, J59.4, J60.4, R29.1, U15.3
SCL15: J61.4, J62.3, J63.4, J64.4, R31.1, U16.3
SCL16: J65.4, J66.3, J67.4, J68.4, R33.1, U17.3
SCL17: J69.4, J70.3, J71.4, J72.4, R35.1, U18.3
SCL18: J73.4, J74.3, J75.4, J76.4, R37.1, U19.3
SCL19: J77.4, J78.3, J79.4, J80.4, R39.1, U20.3
SCL20: J81.4, J82.3, J83.4, J84.4, R41.1, U21.3
SCL21: J85.4, J86.3, J87.4, J88.4, R43.1, U22.3
SCL22: J89.4, J90.3, J91.4, J92.4, R45.1, U23.3
SCL23: J93.4, J94.3, J95.4, J96.4, R47.1, U24.3
SCL24: J97.4, J98.3, J99.4, J100.4, R49.1, U25.3
SCL25: J101.4, J102.3, J103.4, J104.4, R51.1, U26.3
SCL26: J105.4, J106.3, J107.4, J108.4, R53.1, U27.3
SCL27: J109.4, J110.3, J111.4, J112.4, R55.1, U28.3
SCL28: J113.4, J114.3, J115.4, J116.4, R57.1, U29.3
SCL29: J117.4, J118.3, J119.4, J120.4, R59.1, U30.3
SCL30: J121.4, J122.3, J123.4, J124.4, R61.1, U31.3
SCL31: J125.4, J126.3, J127.4, J128.4, R63.1, U32.3
SCL32: J129.4, J130.3, J131.4, J132.4, R65.1, U33.3
SCL33: J133.4, J134.3, J135.4, J136.4, R67.1, U34.3
SCL34: J137.4, J138.3, J139.4, J140.4, R69.1, U35.3
SCL35: J141.4, J142.3, J143.4, J144.4, R71.1, U36.3
SCL36: J145.4, J146.3, J147.4, J148.4, R73.1, U37.3
SCL37: J149.4, J150.3, J151.4, J152.4, R75.1, U38.3
SCL38: J153.4, J154.3, J155.4, J156.4, R77.1, U39.3
SCL39: J157.4, J158.3, J159.4, J160.4, R79.1, U40.3
SCL40: J161.4, J162.3, J163.4, J164.4, R81.1, U41.3
SCL41: J165.4, J166.3, J167.4, J168.4, R83.1, U42.3
SCL42: J169.4, J170.3, J171.4, J172.4, R85.1, U43.3
SCL43: J173.4, J174.3, J175.4, J176.4, R87.1, U44.3
SCL44: J177.4, J178.3, J179.4, J180.4, R89.1, U45.3
SCL45: J181.4, J182.3, J183.4, J184.4, R91.1, U46.3
SCL46: J185.4, J186.3, J187.4, J188.4, R93.1, U47.3
SCL47: J189.4, J190.3, J191.4, J192.4, R95.1, U48.3
SCL48: J193.4, J194.3, J195.4, J196.4, R97.1, U49.3
SCL49: J197.4, J198.3, J199.4, J200.4, R99.1, U50.3
SDA: J1.3, J2.5, J3.3, J4.3, R2.1, U1.5
SDA1: J5.3, J6.5, J7.3, J8.3, R4.1, U2.5
SDA2: J9.3, J10.5, J11.3, J12.3, R6.1, U3.5
SDA3: J13.3, J14.5, J15.3, J16.3, R8.1, U4.5
SDA4: J17.3, J18.5, J19.3, J20.3, R10.1, U5.5
SDA5: J21.3, J22.5, J23.3, J24.3, R12.1, U6.5
SDA6: J25.3, J26.5, J27.3, J28.3, R14.1, U7.5
SDA7: J29.3, J30.5, J31.3, J32.3, R16.1, U8.5
SDA8: J33.3, J34.5, J35.3, J36.3, R18.1, U9.5
SDA9: J37.3, J38.5, J39.3, J40.3, R20.1, U10.5
SDA10: J41.3, J42.5, J43.3, J44.3, R22.1, U11.5
SDA11: J45.3, J46.5, J47.3, J48.3, R24.1, U12.5
SDA12: J49.3, J50.5, J51.3, J52.3, R26.1, U13.5
SDA13: J53.3, J54.5, J55.3, J56.3, R28.1, U14.5
SDA14: J57.3, J58.5, J59.3, J60.3, R30.1, U15.5
SDA15: J61.3, J62.5, J63.3, J64.3, R32.1, U16.5
SDA16: J65.3, J66.5, J67.3, J68.3, R34.1, U17.5
SDA17: J69.3, J70.5, J71.3, J72.3, R36.1, U18.5
SDA18: J73.3, J74.5, J75.3, J76.3, R38.1, U19.5
SDA19: J77.3, J78.5, J79.3, J80.3, R40.1, U20.5
SDA20: J81.3, J82.5, J83.3, J84.3, R42.1, U21.5
SDA21: J85.3, J86.5, J87.3, J88.3, R44.1, U22.5
SDA22: J89.3, J90.5, J91.3, J92.3, R46.1, U23.5
SDA23: J93.3, J94.5, J95.3, J96.3, R48.1, U24.5
SDA24: J97.3, J98.5, J99.3, J100.3, R50.1, U25.5
SDA25: J101.3, J102.5, J103.3, J104.3, R52.1, U26.5
SDA26: J105.3, J106.5, J107.3, J108.3, R54.1, U27.5
SDA27: J109.3, J110.5, J111.3, J112.3, R56.1, U28.5
SDA28: J113.3, J114.5, J115.3, J116.3, R58.1, U29.5
SDA29: J117.3, J118.5, J119.3, J120.3, R60.1, U30.5
SDA30: J121.3, J122.5, J123.3, J124.3, R62.1, U31.5
SDA31: J125.3, J126.5, J127.3, J128.3, R64.1, U32.5
SDA32: J129.3, J130.5, J131.3, J132.3, R66.1, U33.5
SDA33: J133.3, J134.5, J135.3, J136.3, R68.1, U34.5
SDA34: J137.3, J138.5, J139.3, J140.3, R70.1, U35.5
SDA35: J141.3, J142.5, J143.3, J144.3, R72.1, U36.5
SDA36: J145.3, J146.5, J147.3, J148.3, R74.1, U37.5
SDA37: J149.3, J150.5, J151.3, J152.3, R76.1, U38.5
SDA38: J153.3, J154.5, J155.3, J156.3, R78.1, U39.5
SDA39: J157.3, J158.5, J159.3, J160.3, R80.1, U40.5
SDA40: J161.3, J162.5, J163.3, J164.3, R82.1, U41.5
SDA41: J165.3, J166.5, J167.3, J168.3, R84.1, U42.5
SDA42: J169.3, J170.5, J171.3, J172.3, R86.1, U43.5
SDA43: J173.3, J174.5, J175.3, J176.3, R88.1, U44.5
SDA44: J177.3, J178.5, J179.3, J180.3, R90.1, U45.5
SDA45: J181.3, J182.5, J183.3, J184.3, R92.1, U46.5
SDA46: J185.3, J186.5, J187.3, J188.3, R94.1, U47.5
SDA47: J189.3, J190.5, J191.3, J192.3, R96.1, U48.5
SDA48: J193.3, J194.5, J195.3, J196.3, R98.1, U49.5
SDA49: J197.3, J198.5, J199.3, J200.3, R100.1, U50.5
TRIG: J1.6, U1.7
TRIG1: J5.6, U2.7
TRIG2: J9.6, U3.7
TRIG3: J13.6, U4.7
TRIG4: J17.6, U5.7
TRIG5: J21.6, U6.7
TRIG6: J25.6, U7.7
TRIG7: J29.6, U8.7
TRIG8: J33.6, U9.7
TRIG9: J37.6, U10.7
TRIG10: J41.6, U11.7
TRIG11: J45.6, U12.7
TRIG12: J49.6, U13.7
TRIG13: J53.6, U14.7
TRIG14: J57.6, U15.7
TRIG15: J61.6, U16.7
TRIG16: J65.6, U17.7
TRIG17: J69.6, U18.7
TRIG18: J73.6, U19.7
TRIG19: J77.6, U20.7
TRIG20: J81.6, U21.7
TRIG21: J85.6, U22.7
TRIG22: J89.6, U23.7
TRIG23: J93.6, U24.7
TRIG24: J97.6, U25.7
TRIG25: J101.6, U26.7
TRIG26: J105.6, U27.7
TRIG27: J109.6, U28.7
TRIG28: J113.6, U29.7
TRIG29: J117.6, U30.7
TRIG30: J121.6, U31.7
TRIG31: J125.6, U32.7
TRIG32: J129.6, U33.7
TRIG33: J133.6, U34.7
TRIG34: J137.6, U35.7
TRIG35: J141.6, U36.7
TRIG36: J145.6, U37.7
TRIG37: J149.6, U38.7
TRIG38: J153.6, U39.7
TRIG39: J157.6, U40.7
TRIG40: J161.6, U41.7
TRIG41: J165.6, U42.7
TRIG42: J169.6, U43.7
TRIG43: J173.6, U44.7
TRIG44: J177.6, U45.7
TRIG45: J181.6, U46.7
TRIG46: J185.6, U47.7
TRIG47: J189.6, U48.7
TRIG48: J193.6, U49.7
TRIG49: J197.6, U50.7

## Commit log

2019-05-22 removed useless file
2019-05-22 Added compile error to help debug
2019-05-22 Fixed some bugs
2019-05-22 Trying to fixe lib issue
2019-05-22 Still trying to fix the lib
2019-05-22 One last problem before something might work
    "multiple definition of"
    For more detail check: Compiling error.txt
2019-05-22 Done! Compiles has to be tested
2019-05-23 MLX lib properly done, choose address for left and right
    Next step support screen and test RC03
2019-05-23 added support for sh1106
2019-05-23 Display not working
    appears to be a refresh problem
2019-05-23 Went back to U8g2 Lib for screen but still no display
    Need to fix u8g2 to make screen work (maybe conflict with mlx?)
2019-05-23 Got the screen working
    need to fix the startup bmp
2019-05-23 Screen is working
    need to fix delay of navigation switch
2019-05-23 Made a short description of the project
2019-05-25 Done with RC03 SBus is working
2019-05-25 Beginning of RC04
    Goals:
    -Buttons:
    -Read nav joystick capacity
    -Add 6 channels from buttons and pots
    -Add SoftPower
2019-05-25 Added OTA back
2019-05-28 RC04 updated for gl200a pcb
    added joystick for nav, buttons (all but c1 & c2)
2019-05-29 added "rs latch" to arm and rth
2019-06-04 late update don't know what changed
2019-06-11 added mavlink doc for futur implementation
2019-06-11 no change to code
2019-06-13 Started Soft power code in button.h
2019-06-13 Started some big changes in code design
    added .h files to clarify code
2019-06-18 Code compiles, not tested yet on hardware
2019-06-19 removed bind option for X modules
2019-06-19 added compile choice between sbus and mavlink
2019-06-19 Need to fix soft power, doesn't work
2019-06-20 cleaned master sources
2019-06-20 added master opentx
2019-06-26 trying to add softpower but not easy
2019-07-10 Updated the release candidate guide
2019-07-12 Made some minor changes
    done the left pot mode switch
2019-07-17 RC05 Started
2019-07-19 MavLink should work by now
2019-07-20 working on softpower
2019-08-02 working on the hardware of RC04
    too much latency, trying to figure it out
2019-08-14 fixing the mlx problem on esp32 (RC04)
2019-08-22 trying to figure out some problem with SBus
    Added simple PPM version to make sure mlx was working
    Finally fixed the MLX issue on ESP32 (if data>60000 then data = data - 60000) easy fix, seems to work fine though
2019-08-22 Fixed RC04
2019-12-26 started a new branch to accomodate dualcore
2020-03-03 PXX is the way to go for R9M
2020-10-22 Actually using an Arduino pro mini to create PXX
2020-10-22 updated dual core version
2020-11-03 PXX generated by esp32 is almost there
2020-11-03 working on pxx in pumatx_32 problem with put_pcm_byte()
    dualcore version isnt working yet
2020-11-04 PXX works!!!
2020-11-04 PXX works!!!
    code is in PumaTX_32
    some cleaning is required but it is good for now!
2020-11-04 code is cleanner now
2020-11-05 Started PumaTX_32 branch
    PumaTX_32_RC04 is done, basic PXX is working.
    RC05 goal is to not break it and add dual core usage
2020-11-08 removed digitalRead for esp32 specific commands
2020-11-08 started to think about custom radio module sx1280
2020-11-20 started reverse engineering the mavic controller dispaly
2020-11-20 used for
2020-11-20 figuring out which bit turns on which part of the display
2020-11-23 added scroll function for the 11 14 segments display
2020-11-23 everything is working pretty well
    set_text() and set_name() need optimisation for scrolling text while not freezing the rest of the screen
2020-11-23 surprise
2020-12-02 added pumatx32_RC4.1
    pumatx32_RC4.1 is a version where the display and mlx libs have been added and tested
2020-12-02 made some small adjustements to rcdata in pumatx32_RC4.1
2020-12-05 Starting RC05
    RC04.1 added display and mlx libs.
    Both are working, only delay between pxx pulses have been increased: solution: dualcore -> going on RC05 for dualcore functionnality
2021-01-07 started doing a pptx to organize the code
2021-01-27 Fixed some bugs with the display
    The display seems to be loosing connection sometimes, so re initialising the library seems to be a quick fix. (calling display.begin each time to update it)
    Don't know if the issue is on hardware side or softare side
    I tried with a new display and ribbon plug (FPC 12P 0.5mm)
2021-02-01 remade file organisation for better use of vs code git functionnality
2021-02-01 added elrs
2021-02-01 little change to comment
2021-09-12 Back to the project, added HSIS
    Changes to be committed:
    modified: Other/_Master Program for sourcing code/ExpressLRS-master/src/src/tx_main.cpp
    modified: old/PumaTX_display/PumaTX_display.ino
    modified: old/PumaTX_display/display.cpp
    modified: old/PumaTX_display/display.h
    modified: platformio.ini
2021-09-12 modified: README.md
2021-09-13 made changes to dualcore functions
2021-09-13 removed a lot of useless files
2021-09-13 new file: Organisation/ESP32 HSIS.xlsx
2021-09-13 added files (doc, orga, old, pcb, test)
2021-09-14 fixed dualcore no delay
2021-09-16 Started aading components schematics to PumaTX KiCAD's library
2021-09-17 added EMH3 dual transistor schematic's to pumalib
2021-09-17 added flash chip W25Q32JVZPIQ to puma lib
2021-09-21 added components to pumalib
2021-09-22 changed organisation new file: pcb/datasheet/ESP32/esp32_datasheet_en.pdf new file: pcb/datasheet/ESP32/esp32_hardware_design_guidelines_en.pdf new file: pcb/datasheet/ESP32/esp32_technical_reference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
2021-09-22 modified: pcb/Tx_mother_board/Tx_mother_board/PumaTx.dcm modified: pcb/Tx_mother_board/Tx_mother_board/PumaTx.lib new file: pcb/datasheet/AP7343Q.pdf new file: pcb/datasheet/esp32_datasheet_en.pdf
2021-09-23 added new component to kicad lib
2022-05-23 Working a bit on the schematic
2022-07-07 Finally, the real schematic is coming
2022-07-10 Updated folder structure
2022-07-10 Added E28-2G4M27S
2022-07-13 Small updates around SX1280
2022-07-16 Updated schematic
2022-07-16 Updated schematics
2022-07-18 Started a rough layout
2022-07-20 Started working on the power part
2022-07-20 Started pinout of button flex
2022-07-20 quick schematic update
2022-07-20 Flex pinout added to schematic
2022-07-20 Added some footprints
2022-07-25 small updates
2022-07-25 Added display consumption
2022-07-25 Minor updates
2022-07-28 Changed motor and fan schematics
2022-07-29 Finished BQ, EPS32 integration
2022-07-29 Added pptx of PCBs analysis
2022-07-30 Almost done!
2022-08-01 Schematic is "done"
    Functionaly it is done, but could get some cleanup
2022-08-04 started some software tests
2022-08-04 looking at simpleTX CRSF implementation
2022-08-04 cleanup of schematic
2022-08-07 Added license
2022-08-07 quick folder organisation modification
2022-08-08 cleanup
2022-08-11 Generated BOM and changed 2 capa footprints
2022-08-11 updated bom
2022-08-12 newer backup
2022-08-17 PCB layout is done, routing to go!
2022-08-17 quick layout update
2022-08-18 added mouser cart
2022-08-18 Started layout
2022-08-18 updated layout
2022-08-22 Continued routing
2022-09-07 quick esp32 update
2022-09-12 working on routing / placement
2022-09-13 Quick update
2022-09-13 Routing update
2022-09-14 Done SX1280 routing and half of RF
2022-09-14 routing is ongoing
2022-09-15 rf backup
2022-09-15 some changes on routing, every QFN is on the same side
2022-09-16 Routing goes on and on and on...
2022-09-17 and on and on and on... It is getting harder
2022-09-18 Wow its gonna be complicated
2022-09-19 Almost done !! only 3 PSU to go
2022-09-19 Is this the end? or is it just the beginning?
2022-09-19 Order done. Is it a mistake? maybe...
2022-09-22 Lets go for software
2022-09-25 started working on configurator
2022-09-26 quick tries on objectifying I2C class or something like that
2022-09-26 GUI working (lol no)
2022-09-27 small corrections
2022-09-28 Updated mlx and display lib to input i2c object
2022-09-28 it builds!!!
2022-10-05 software fix
2022-10-05 Fixed I2C error, display bus wasnt initialized
2022-10-05 changed function timing
2022-10-06 added more detail about gpio requierment
2022-10-06 created PUMATX_MB_HW01 and added patch to HW00
2022-10-06 hw01
2022-10-09 button bringup
2022-10-09 button bringup 2
2022-10-10 Button and battery bringup done
2022-10-11 haptic bringup done / DB_HW00 started
2022-10-11 I2C scanner added
2022-10-13 mlx i2c is working
2022-10-13 MLX data seems all good, need to try with gimbals. Channel data is good
2022-10-16 preliminary work on crsf integration
2022-10-17 Display works <3
2022-10-19 Battery reading is shown on display
2022-10-19 Menu navigation is working ✅
2022-10-19 display I2C clock at 1MHz
2022-10-19 quick comment
2022-10-19 Display refresh optimisation
2022-10-20 display optimisation, down to 118us/loop
2022-10-20 updated navigation menu
2022-10-20 display string on 7 segment
2022-10-20 Added function management
2022-10-22 added inBetweenTime
2022-10-22 inBetweenTime added
2022-10-23 function's telemetry was a mess, did some cleanup
2022-10-23 added haptic function
2022-10-23 small cahnges
2022-10-25 trying to add crsf
2022-10-25 lol fixed yesterday issue
2022-10-25 started working on display.off(0b000); feature
2022-10-31 code cleanup
2023-03-08 moved mecha parts to folder
2025-01-13 MB_00 schematic done
2025-01-15 added comments to main.cpp
2025-01-16 just a test
2025-01-18 updated display connector
2025-01-25 cleaning
2025-03-02 worked on mb_01 schematic
2025-04-02 started schematics of LR1121
2026-05-28 Converted solidworks files to STEP
